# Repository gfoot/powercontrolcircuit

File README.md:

# Soft Power Switch Circuit with Tunable Overcurrent Protection Cutoff

 |  | 
:----:|:----:|:----:
Assembled on breadboard | Assembled on veroboard | Demo video

This is a circuit for soft-switching a 5V DC input, with a configurable current limit cutoff, tested from around 10mA up to 1.2A.

This is useful because it protects your power supply, wiring, and components against adverse effects due to things like 
short circuiting, accidental reversed power polarity, placing components incorrectly or backwards in a circuit, or other
component failure.

It's not a boost/buck converter or regulator, just a switch for an existing regulated DC input.

## Operation

Press SW1 to turn the power on.  The LED indicates that power is on.  Press SW2 to turn the power off.

Use RV2 and RV3 to tune the range of currents that are selectable.  See [configuration guide](docs/configuration.md) for the tuning procedure.

Once tuned, RV1 selects the current limit.  When more than this amount of current is drawn, the circuit automatically powers off.

## Schematic

## Bill of Materials

| Ref    | Qty  | Spec     | Notes |
| ------ |:----:| ----     | ----- |
| Q1-2   |   2  | IRF9540N | P-channel power MOSFET - ideally low RDS(on) at VGS=-4.25V |
| Q3     |   1  | 2N3904   | NPN BJT transistor |
| R1-5   |   5  | 10K      | Resistor |
| R6     |   1  | ~0.1 ohm | Power resistor, 1A continuous current, at least 1W recommended |
| R7-8   |   2  | 47K      | Resistor |
| RV1-2  |   2  | 3K       | Trim pots |
| RV3    |   1  | 10K      | Potentiometer |
| U1     |   1  | LM385    | Operational amplifier |
| C1     |   1  | 10u      | Capacitor to prevent accidental power-on (may not be necessary) |

Exact component choices are not critical.  With the above components, and 6x1ohm 250mW resistors in parallel for R6, at a continuous 1A load, 
the resistors get slightly warm to the touch and the MOSFET tabs measure 60C-70C, in open air with no heatsinks or active cooling.

The added output impedance appears to be approximately 0.75 ohms with these components, at a load current of 1A; lower currents 
lead to lower impedance.  Choosing Q1-2 with lower RDS(on) at -4.25V or more will have the greatest effect on impedance.

## Improvements

I'm considering the following:

* Use a charge pump to lower the gate voltage to Q1-2, to improve impedance at high loads
* Configure the op amp with feedback to amplify the voltage difference, in case it makes tuning the cutoff simpler
* Add an optional linear regulator to guarantee output voltage at high loads

Other suggestions very welcome!

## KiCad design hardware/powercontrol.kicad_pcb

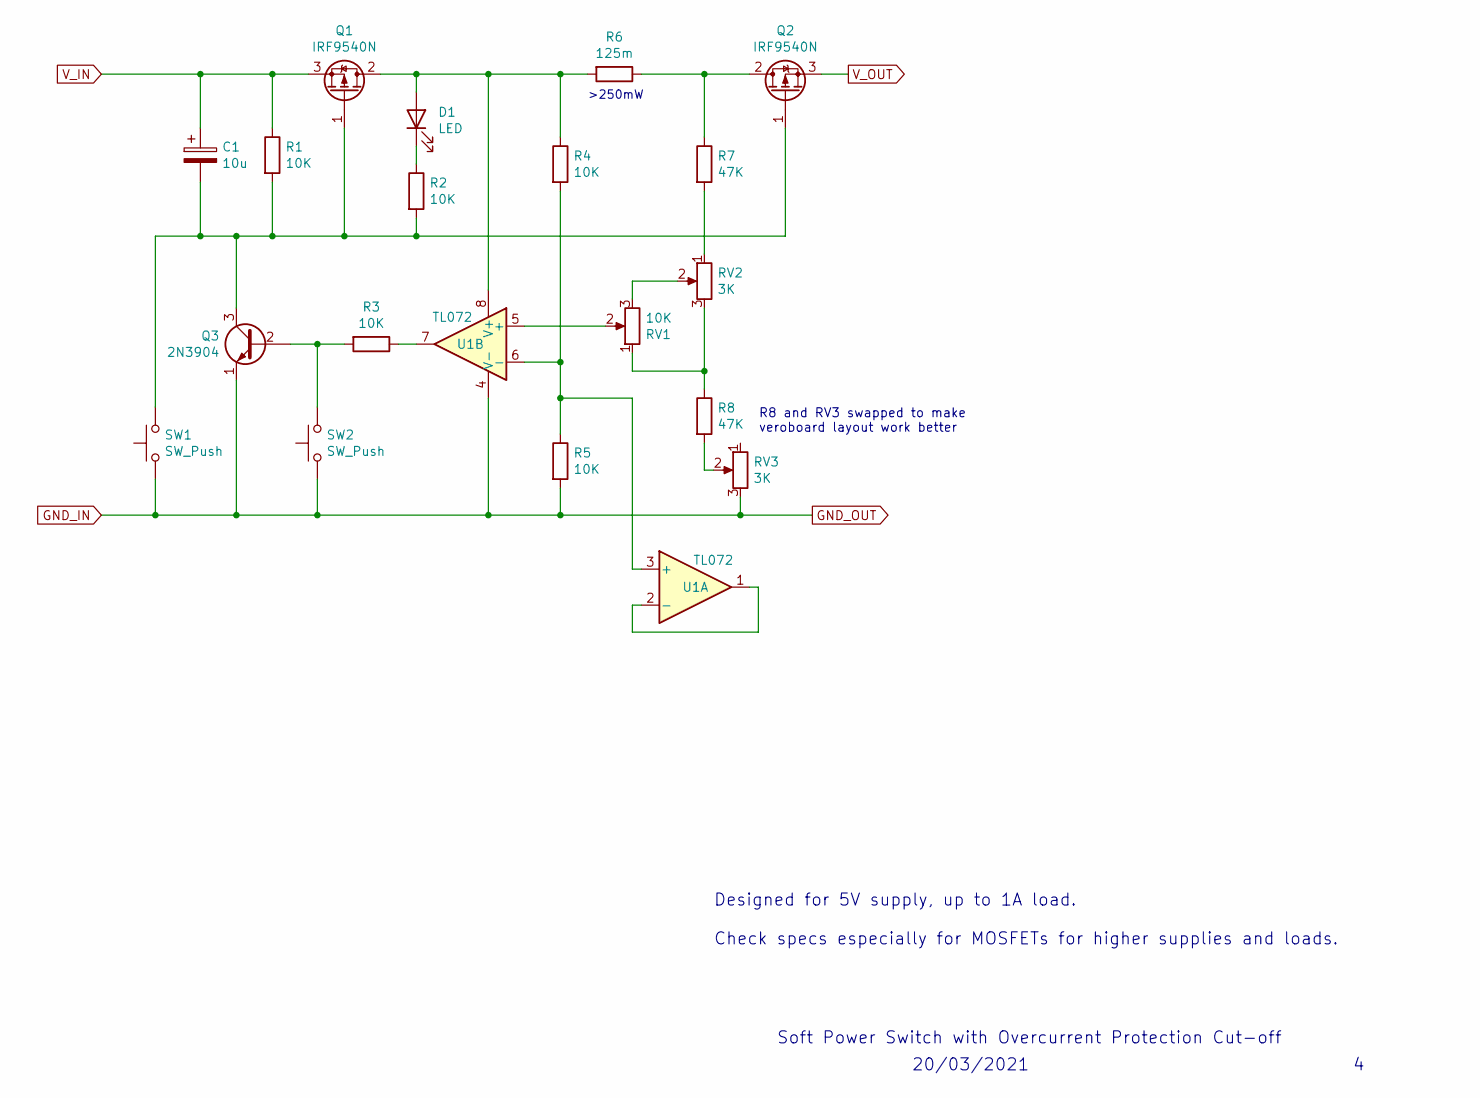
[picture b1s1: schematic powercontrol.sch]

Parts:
C1: 10u; CP_Radial_D5.0mm_P2.50mm
D1: LED; LED_D3.0mm
Q1, Q2: IRF9540N; TO-220-3_Vertical
Q3: 2N3904; TO-92_Inline_Wide
R1, R2, R3, R4, R5: 10K; R_Axial_DIN0204_L3.6mm_D1.6mm_P7.62mm_Horizontal
R6: 125m; R_Axial_Power_L20.0mm_W6.4mm_P25.40mm
R7, R8: 47K; R_Axial_DIN0204_L3.6mm_D1.6mm_P7.62mm_Horizontal
RV1: 10K; Potentiometer_Vishay_T73YP_Vertical
RV2, RV3: 3K; Potentiometer_Runtron_RM-065_Vertical
SW1, SW2: SW_Push; SW_PUSH_6mm_H5mm
U1: TL072; DIP-8_W7.62mm

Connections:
GND_IN: Q3.1 (E), R5.2, RV3.3, SW1.2, SW2.2, U1.4 (V-)
unnamed: C1.2, Q1.1 (G), Q2.1 (G), Q3.3 (C), R1.2, R2.2, SW1.1
unnamed: D1.1 (K), R2.1
unnamed: D1.2 (A), Q1.2 (D), R4.1, R6.2, U1.8 (V+)
unnamed: Q2.2 (D), R6.1, R7.1
unnamed: Q3.2 (B), R3.2, SW2.1
unnamed: R3.1, U1.7
unnamed: R4.2, R5.1, U1.3 (+), U1.6 (-)
unnamed: R7.2, RV2.1
unnamed: R8.1, RV1.1, RV2.3
unnamed: R8.2, RV3.2
unnamed: RV1.2, U1.5 (+)
unnamed: RV1.3, RV2.2
unnamed: U1.1, U1.2 (-)
V_IN: C1.1, Q1.3 (S), R1.1
V_OUT: Q2.3 (S)

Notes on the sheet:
Soft Power Switch with Overcurrent Protection Cut-off
20/03/2021
Designed for 5V supply, up to 1A load. Check specs especially for MOSFETs for higher supplies and loads.
>250mW
R8 and RV3 swapped to make veroboard layout work better

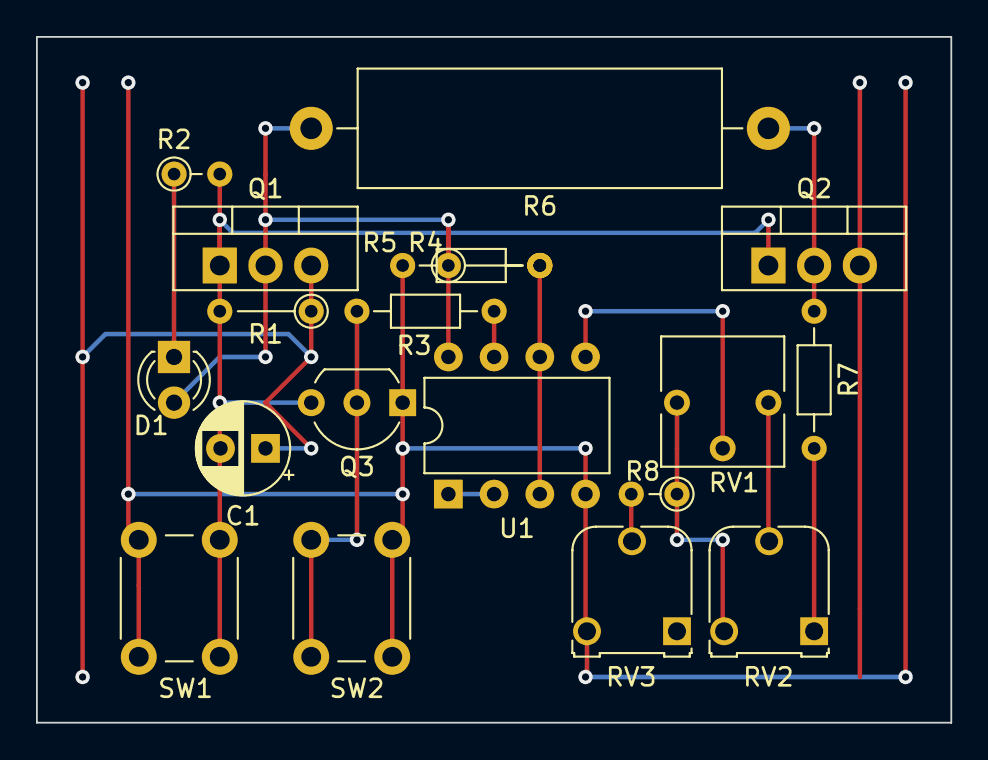
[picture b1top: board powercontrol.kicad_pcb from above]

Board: 2 copper layers, 50.8 x 38.1 mm, 19 parts (0 on the bottom side), 15 nets.

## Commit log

2021-03-20 rev 2 schematic, veroboard layout
2021-03-21 V4 - Veroboard layout fixes, actually built and tested on veroboard now
2021-03-22 Add images of breadboard, veroboard, schematic
2021-03-22 Add configuration instructions
